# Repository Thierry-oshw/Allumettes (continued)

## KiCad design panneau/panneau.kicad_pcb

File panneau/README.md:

# Panelize multiple different designs in KiCAD
Requires KiKit and is based on code from [KiKit](https://github.com/yaqwsx/KiKit/tree/master)

KiKit only allows creating panels of the same design. Creating a panel from multiple boards has too many degrees of freedom to implement in a nice GUI.
Hence, for creating such a panel, a scripting attempt is necessary.

This script creates a simple panel of two different designs of identical dimensions placed above each other.
With including configuration it adds a rail on top and bottom and includes tabs with mouse bites in between boards and between board and rail.

**You will have to adjust the script to your own needs**
This Gist is only meant to provide you with a working example.

## Usage
Install KiKit, start KiCAD command prompt, navigate to appropriate directory, run `python panelize_multiple.py`

## License
Derived from KiKit. Same MIT license.

## Versions
Tested with KiCAD 7 and KiKit 1.1.0

## faire "python panelize_multiple.py" dans le cli kicad
puis changer les v-cut en user.1 au lieu de user.comments

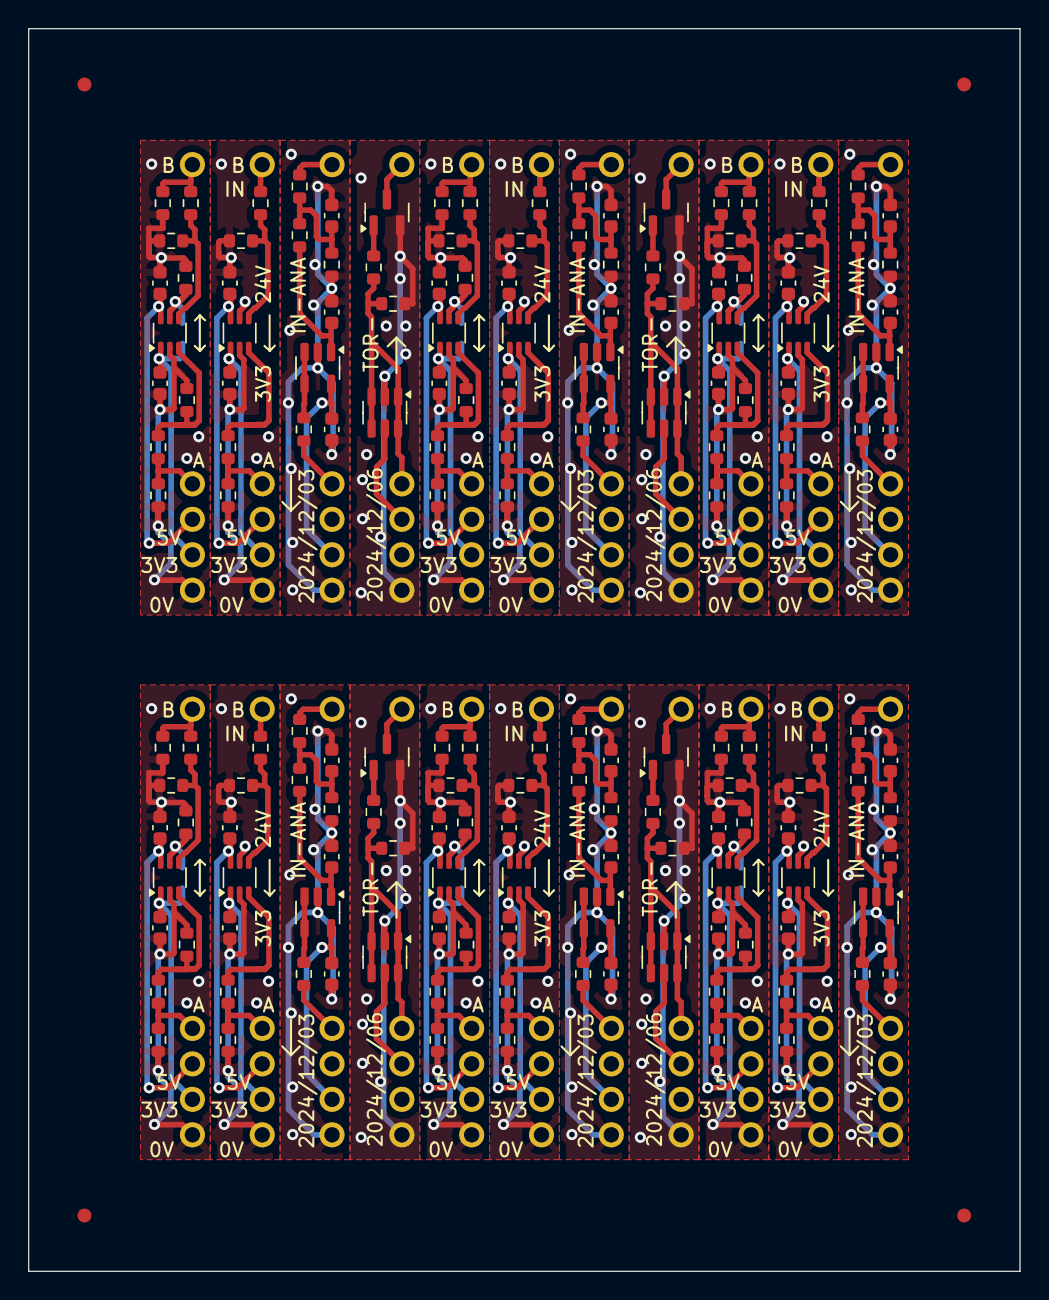
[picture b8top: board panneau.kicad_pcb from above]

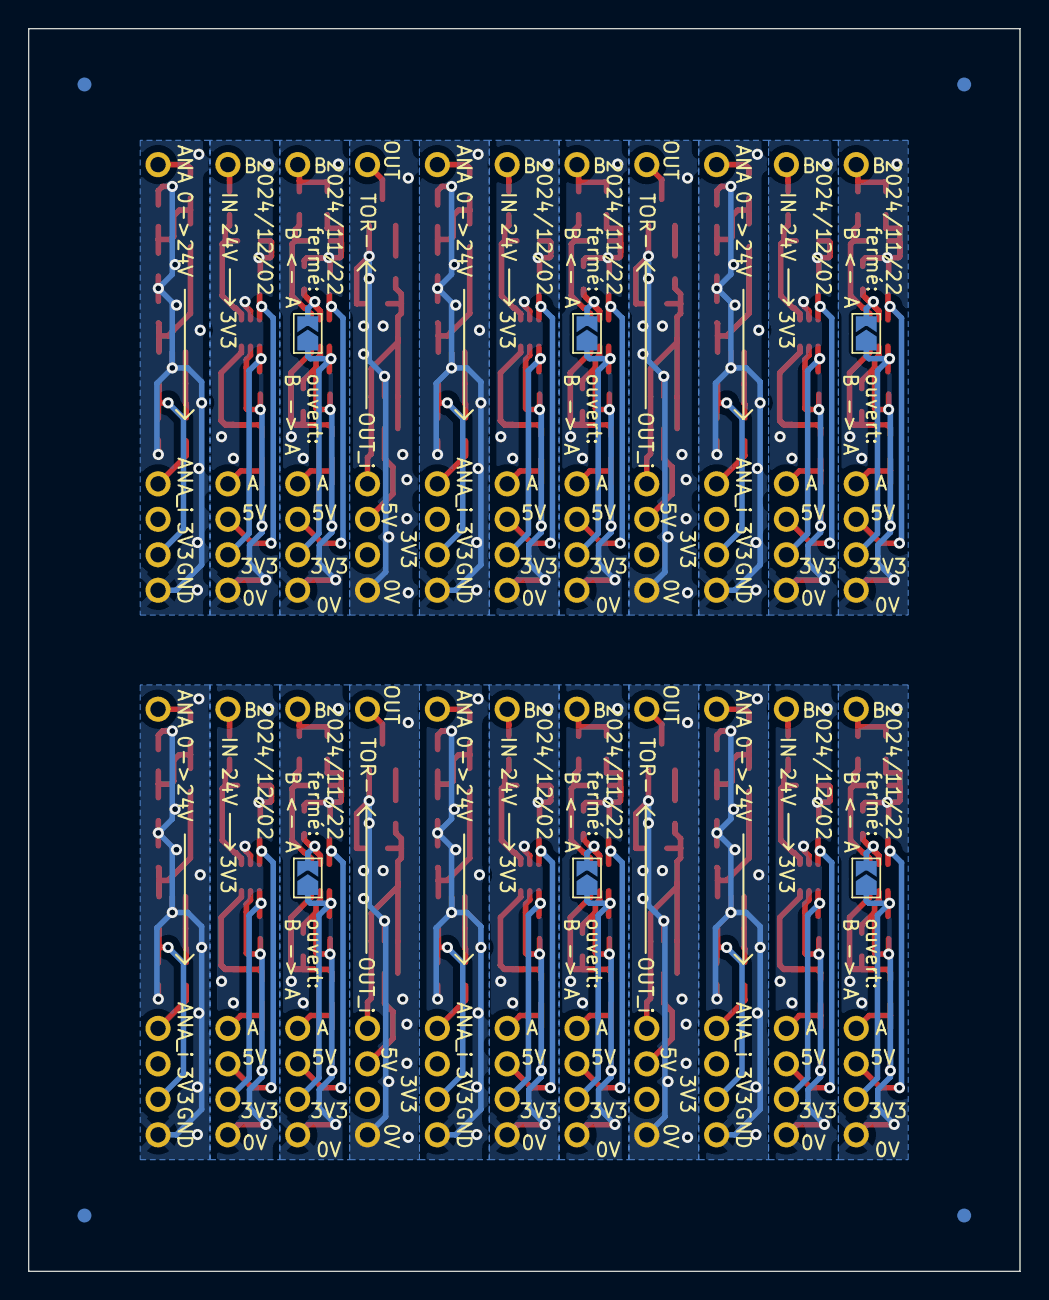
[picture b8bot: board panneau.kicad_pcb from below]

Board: 2 copper layers, 71.0 x 89.0 mm, 290 parts (10 on the bottom side), 152 nets.

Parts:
Board_0-C1, Board_0-C2, Board_1-C1, Board_1-C2, Board_2-C1, Board_2-C9, Board_4-C1, Board_4-C2, Board_5-C1, Board_5-C2, Board_6-C1, Board_6-C9, Board_8-C1, Board_8-C2, Board_9-C1, Board_9-C2, Board_10-C1, Board_10-C9, Board_11-C1, Board_11-C2, Board_12-C1, Board_12-C2, Board_13-C1, Board_13-C9, Board_15-C1, Board_15-C2, Board_16-C1, Board_16-C2, Board_17-C1, Board_17-C9, Board_19-C1, Board_19-C2, Board_20-C1, Board_20-C2, Board_21-C1, Board_21-C9: 100nF 50V X7R; C_0603_1608Metric
Board_0-JP1, Board_4-JP1, Board_8-JP1, Board_11-JP1, Board_15-JP1, Board_19-JP1: SolderJumper_2_Open; SolderJumper-2_P1.3mm_Open_TrianglePad1.0x1.5mm
Board_0-R1, Board_0-R4, Board_0-R7, Board_1-R1, Board_3-R1, Board_4-R1, Board_4-R4, Board_4-R7, Board_5-R1, Board_7-R1, Board_8-R1, Board_8-R4, Board_8-R7, Board_9-R1, Board_11-R1, Board_11-R4, Board_11-R7, Board_12-R1, Board_14-R1, Board_15-R1, Board_15-R4, Board_15-R7, Board_16-R1, Board_18-R1, Board_19-R1, Board_19-R4, Board_19-R7, Board_20-R1: 100k; R_0603_1608Metric
Board_0-R2, Board_0-R6, Board_1-R2, Board_2-R9, Board_2-R13, Board_4-R2, Board_4-R6, Board_5-R2, Board_6-R9, Board_6-R13, Board_8-R2, Board_8-R6, Board_9-R2, Board_10-R9, Board_10-R13, Board_11-R2, Board_11-R6, Board_12-R2, Board_13-R9, Board_13-R13, Board_15-R2, Board_15-R6, Board_16-R2, Board_17-R9, Board_17-R13, Board_19-R2, Board_19-R6, Board_20-R2, Board_21-R9, Board_21-R13: 1k; R_0603_1608Metric
Board_0-R3, Board_0-R5, Board_4-R3, Board_4-R5, Board_8-R3, Board_8-R5, Board_11-R3, Board_11-R5, Board_15-R3, Board_15-R5, Board_19-R3, Board_19-R5: NM; R_0603_1608Metric
Board_0-TP1, Board_0-TP2, Board_0-TP3, Board_0-TP4, Board_0-TP5, Board_1-TP1, Board_1-TP2, Board_1-TP3, Board_1-TP4, Board_1-TP5, Board_2-TP1, Board_2-TP2, Board_2-TP3, Board_2-TP4, Board_2-TP5, Board_3-TP1, Board_3-TP2, Board_3-TP3, Board_3-TP4, Board_3-TP5, Board_4-TP1, Board_4-TP2, Board_4-TP3, Board_4-TP4, Board_4-TP5, Board_5-TP1, Board_5-TP2, Board_5-TP3, Board_5-TP4, Board_5-TP5, Board_6-TP1, Board_6-TP2, Board_6-TP3, Board_6-TP4, Board_6-TP5, Board_7-TP1, Board_7-TP2, Board_7-TP3, Board_7-TP4, Board_7-TP5, Board_8-TP1, Board_8-TP2, Board_8-TP3, Board_8-TP4, Board_8-TP5, Board_9-TP1, Board_9-TP2, Board_9-TP3, Board_9-TP4, Board_9-TP5, Board_10-TP1, Board_10-TP2, Board_10-TP3, Board_10-TP4, Board_10-TP5, Board_11-TP1, Board_11-TP2, Board_11-TP3, Board_11-TP4, Board_11-TP5, Board_12-TP1, Board_12-TP2, Board_12-TP3, Board_12-TP4, Board_12-TP5, Board_13-TP1, Board_13-TP2, Board_13-TP3, Board_13-TP4, Board_13-TP5, Board_14-TP1, Board_14-TP2, Board_14-TP3, Board_14-TP4, Board_14-TP5, Board_15-TP1, Board_15-TP2, Board_15-TP3, Board_15-TP4, Board_15-TP5, Board_16-TP1, Board_16-TP2, Board_16-TP3, Board_16-TP4, Board_16-TP5, Board_17-TP1, Board_17-TP2, Board_17-TP3, Board_17-TP4, Board_17-TP5, Board_18-TP1, Board_18-TP2, Board_18-TP3, Board_18-TP4, Board_18-TP5, Board_19-TP1, Board_19-TP2, Board_19-TP3, Board_19-TP4, Board_19-TP5, Board_20-TP1, Board_20-TP2, Board_20-TP3, Board_20-TP4, Board_20-TP5, Board_21-TP1, Board_21-TP2, Board_21-TP3, Board_21-TP4, Board_21-TP5: TestPoint; Pastille
Board_0-U1, Board_1-U1, Board_4-U1, Board_5-U1, Board_8-U1, Board_9-U1, Board_11-U1, Board_12-U1, Board_15-U1, Board_16-U1, Board_19-U1, Board_20-U1: SN74LVC1T45DCK; SOT-363_SC-70-6
Board_1-R5, Board_5-R5, Board_9-R5, Board_12-R5, Board_16-R5, Board_20-R5: 2k2; R_0603_1608Metric
Board_1-R6, Board_2-R1, Board_5-R6, Board_6-R1, Board_9-R6, Board_10-R1, Board_12-R6, Board_13-R1, Board_16-R6, Board_17-R1, Board_20-R6, Board_21-R1: 10k; R_0603_1608Metric
Board_2-C5, Board_6-C5, Board_10-C5, Board_13-C5, Board_17-C5, Board_21-C5: 1nF 50V X7R; C_0603_1608Metric
Board_2-R2, Board_6-R2, Board_10-R2, Board_13-R2, Board_17-R2, Board_21-R2: 1k5; R_0603_1608Metric
Board_2-U1, Board_6-U1, Board_10-U1, Board_13-U1, Board_17-U1, Board_21-U1: LMV321; SOT-23-5
Board_3-Q1, Board_7-Q1, Board_14-Q1, Board_18-Q1: AO3400A; SOT-23
Board_3-R2, Board_7-R2, Board_14-R2, Board_18-R2: 0R; R_0603_1608Metric
Board_3-U1, Board_7-U1, Board_14-U1, Board_18-U1: SRV05-4; SOT-23-6
KiKit_FID_B_1, KiKit_FID_B_2, KiKit_FID_B_3, KiKit_FID_B_4: Fiducial
KiKit_FID_T_1, KiKit_FID_T_2, KiKit_FID_T_3, KiKit_FID_T_4: Fiducial

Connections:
Board_0-/3V3: Board_0-C1.1, Board_0-JP1.1 (A), Board_0-TP4.1, Board_0-U1.1 (VCCA)
Board_0-/5V: Board_0-C2.1, Board_0-TP3.1, Board_0-U1.6 (VCCB)
Board_0-/GND: Board_0-C1.2, Board_0-C2.2, Board_0-R1.2, Board_0-R3.2, Board_0-R4.2, Board_0-R5.2, Board_0-R7.2, Board_0-TP5.1, Board_0-U1.2 (GND)
Board_0-/OUT: Board_0-R6.2, Board_0-R7.1, Board_0-TP1.1
Board_0-/OUT_i: Board_0-R1.1, Board_0-R2.1, Board_0-TP2.1
Board_0-Net-(JP1-B): Board_0-JP1.2 (B), Board_0-R4.1, Board_0-U1.5 (DIR)
Board_0-Net-(U1-A): Board_0-R2.2, Board_0-R3.1, Board_0-U1.3 (A)
Board_0-Net-(U1-B): Board_0-R5.1, Board_0-R6.1, Board_0-U1.4 (B)
Board_1-/3V3: Board_1-C1.1, Board_1-TP4.1, Board_1-U1.1 (VCCA)
Board_1-/5V: Board_1-C2.1, Board_1-TP3.1, Board_1-U1.6 (VCCB)
Board_1-/GND: Board_1-C1.2, Board_1-C2.2, Board_1-R1.2, Board_1-R5.2, Board_1-TP5.1, Board_1-U1.2 (GND), Board_1-U1.5 (DIR)
Board_1-/IN: Board_1-R6.2, Board_1-TP1.1
Board_1-/IN_i: Board_1-R1.1, Board_1-R2.1, Board_1-TP2.1
Board_1-Net-(U1-A): Board_1-R2.2, Board_1-U1.3 (A)
Board_1-Net-(U1-B): Board_1-R5.1, Board_1-R6.1, Board_1-U1.4 (B)
Board_2-/3V3: Board_2-C9.1, Board_2-TP3.1, Board_2-U1.5 (V+)
Board_2-/ANA: Board_2-R1.2, Board_2-TP1.1
Board_2-/ANA_i: Board_2-R13.2, Board_2-TP2.1
Board_2-/GND: Board_2-C1.2, Board_2-C5.2, Board_2-C9.2, Board_2-R2.1, Board_2-TP4.1, Board_2-U1.2 (V-)
Board_2-Net-(C1-Pad1): Board_2-C1.1, Board_2-R1.1, Board_2-R2.2, Board_2-R9.1
Board_2-Net-(U1-+): Board_2-C5.1, Board_2-R9.2, Board_2-U1.1 (+)
Board_2-Net-(U1--): Board_2-R13.1, Board_2-U1.3 (-), Board_2-U1.4
Board_3-/0V: Board_3-Q1.2 (S), Board_3-R1.2, Board_3-TP5.1, Board_3-U1.2 (VN)
Board_3-/5V: Board_3-TP3.1, Board_3-U1.5 (VP)
Board_3-/OUT: Board_3-Q1.3 (D), Board_3-TP1.1
Board_3-/OUT_i: Board_3-R1.1, Board_3-R2.1, Board_3-TP2.1, Board_3-U1.1 (IO1), Board_3-U1.3 (IO2), Board_3-U1.4 (IO3), Board_3-U1.6 (IO4)
Board_3-Net-(Q1-G): Board_3-Q1.1 (G), Board_3-R2.2
Board_4-/3V3: Board_4-C1.1, Board_4-JP1.1 (A), Board_4-TP4.1, Board_4-U1.1 (VCCA)
Board_4-/5V: Board_4-C2.1, Board_4-TP3.1, Board_4-U1.6 (VCCB)
Board_4-/GND: Board_4-C1.2, Board_4-C2.2, Board_4-R1.2, Board_4-R3.2, Board_4-R4.2, Board_4-R5.2, Board_4-R7.2, Board_4-TP5.1, Board_4-U1.2 (GND)
Board_4-/OUT: Board_4-R6.2, Board_4-R7.1, Board_4-TP1.1
Board_4-/OUT_i: Board_4-R1.1, Board_4-R2.1, Board_4-TP2.1
Board_4-Net-(JP1-B): Board_4-JP1.2 (B), Board_4-R4.1, Board_4-U1.5 (DIR)
Board_4-Net-(U1-A): Board_4-R2.2, Board_4-R3.1, Board_4-U1.3 (A)
Board_4-Net-(U1-B): Board_4-R5.1, Board_4-R6.1, Board_4-U1.4 (B)
Board_5-/3V3: Board_5-C1.1, Board_5-TP4.1, Board_5-U1.1 (VCCA)
Board_5-/5V: Board_5-C2.1, Board_5-TP3.1, Board_5-U1.6 (VCCB)
Board_5-/GND: Board_5-C1.2, Board_5-C2.2, Board_5-R1.2, Board_5-R5.2, Board_5-TP5.1, Board_5-U1.2 (GND), Board_5-U1.5 (DIR)
Board_5-/IN: Board_5-R6.2, Board_5-TP1.1
Board_5-/IN_i: Board_5-R1.1, Board_5-R2.1, Board_5-TP2.1
Board_5-Net-(U1-A): Board_5-R2.2, Board_5-U1.3 (A)
Board_5-Net-(U1-B): Board_5-R5.1, Board_5-R6.1, Board_5-U1.4 (B)
Board_6-/3V3: Board_6-C9.1, Board_6-TP3.1, Board_6-U1.5 (V+)
Board_6-/ANA: Board_6-R1.2, Board_6-TP1.1
Board_6-/ANA_i: Board_6-R13.2, Board_6-TP2.1
Board_6-/GND: Board_6-C1.2, Board_6-C5.2, Board_6-C9.2, Board_6-R2.1, Board_6-TP4.1, Board_6-U1.2 (V-)
Board_6-Net-(C1-Pad1): Board_6-C1.1, Board_6-R1.1, Board_6-R2.2, Board_6-R9.1
Board_6-Net-(U1-+): Board_6-C5.1, Board_6-R9.2, Board_6-U1.1 (+)
Board_6-Net-(U1--): Board_6-R13.1, Board_6-U1.3 (-), Board_6-U1.4
Board_7-/0V: Board_7-Q1.2 (S), Board_7-R1.2, Board_7-TP5.1, Board_7-U1.2 (VN)
Board_7-/5V: Board_7-TP3.1, Board_7-U1.5 (VP)
Board_7-/OUT: Board_7-Q1.3 (D), Board_7-TP1.1
Board_7-/OUT_i: Board_7-R1.1, Board_7-R2.1, Board_7-TP2.1, Board_7-U1.1 (IO1), Board_7-U1.3 (IO2), Board_7-U1.4 (IO3), Board_7-U1.6 (IO4)
Board_7-Net-(Q1-G): Board_7-Q1.1 (G), Board_7-R2.2
Board_8-/3V3: Board_8-C1.1, Board_8-JP1.1 (A), Board_8-TP4.1, Board_8-U1.1 (VCCA)
Board_8-/5V: Board_8-C2.1, Board_8-TP3.1, Board_8-U1.6 (VCCB)
Board_8-/GND: Board_8-C1.2, Board_8-C2.2, Board_8-R1.2, Board_8-R3.2, Board_8-R4.2, Board_8-R5.2, Board_8-R7.2, Board_8-TP5.1, Board_8-U1.2 (GND)
Board_8-/OUT: Board_8-R6.2, Board_8-R7.1, Board_8-TP1.1
Board_8-/OUT_i: Board_8-R1.1, Board_8-R2.1, Board_8-TP2.1
Board_8-Net-(JP1-B): Board_8-JP1.2 (B), Board_8-R4.1, Board_8-U1.5 (DIR)
Board_8-Net-(U1-A): Board_8-R2.2, Board_8-R3.1, Board_8-U1.3 (A)
Board_8-Net-(U1-B): Board_8-R5.1, Board_8-R6.1, Board_8-U1.4 (B)
Board_9-/3V3: Board_9-C1.1, Board_9-TP4.1, Board_9-U1.1 (VCCA)
Board_9-/5V: Board_9-C2.1, Board_9-TP3.1, Board_9-U1.6 (VCCB)
Board_9-/GND: Board_9-C1.2, Board_9-C2.2, Board_9-R1.2, Board_9-R5.2, Board_9-TP5.1, Board_9-U1.2 (GND), Board_9-U1.5 (DIR)
Board_9-/IN: Board_9-R6.2, Board_9-TP1.1
Board_9-/IN_i: Board_9-R1.1, Board_9-R2.1, Board_9-TP2.1
Board_9-Net-(U1-A): Board_9-R2.2, Board_9-U1.3 (A)
Board_9-Net-(U1-B): Board_9-R5.1, Board_9-R6.1, Board_9-U1.4 (B)
Board_10-/3V3: Board_10-C9.1, Board_10-TP3.1, Board_10-U1.5 (V+)
Board_10-/ANA: Board_10-R1.2, Board_10-TP1.1
Board_10-/ANA_i: Board_10-R13.2, Board_10-TP2.1
Board_10-/GND: Board_10-C1.2, Board_10-C5.2, Board_10-C9.2, Board_10-R2.1, Board_10-TP4.1, Board_10-U1.2 (V-)
Board_10-Net-(C1-Pad1): Board_10-C1.1, Board_10-R1.1, Board_10-R2.2, Board_10-R9.1
Board_10-Net-(U1-+): Board_10-C5.1, Board_10-R9.2, Board_10-U1.1 (+)
Board_10-Net-(U1--): Board_10-R13.1, Board_10-U1.3 (-), Board_10-U1.4
Board_11-/3V3: Board_11-C1.1, Board_11-JP1.1 (A), Board_11-TP4.1, Board_11-U1.1 (VCCA)
Board_11-/5V: Board_11-C2.1, Board_11-TP3.1, Board_11-U1.6 (VCCB)
Board_11-/GND: Board_11-C1.2, Board_11-C2.2, Board_11-R1.2, Board_11-R3.2, Board_11-R4.2, Board_11-R5.2, Board_11-R7.2, Board_11-TP5.1, Board_11-U1.2 (GND)
Board_11-/OUT: Board_11-R6.2, Board_11-R7.1, Board_11-TP1.1
Board_11-/OUT_i: Board_11-R1.1, Board_11-R2.1, Board_11-TP2.1
Board_11-Net-(JP1-B): Board_11-JP1.2 (B), Board_11-R4.1, Board_11-U1.5 (DIR)
Board_11-Net-(U1-A): Board_11-R2.2, Board_11-R3.1, Board_11-U1.3 (A)
Board_11-Net-(U1-B): Board_11-R5.1, Board_11-R6.1, Board_11-U1.4 (B)
Board_12-/3V3: Board_12-C1.1, Board_12-TP4.1, Board_12-U1.1 (VCCA)
Board_12-/5V: Board_12-C2.1, Board_12-TP3.1, Board_12-U1.6 (VCCB)
Board_12-/GND: Board_12-C1.2, Board_12-C2.2, Board_12-R1.2, Board_12-R5.2, Board_12-TP5.1, Board_12-U1.2 (GND), Board_12-U1.5 (DIR)
Board_12-/IN: Board_12-R6.2, Board_12-TP1.1
Board_12-/IN_i: Board_12-R1.1, Board_12-R2.1, Board_12-TP2.1
Board_12-Net-(U1-A): Board_12-R2.2, Board_12-U1.3 (A)
Board_12-Net-(U1-B): Board_12-R5.1, Board_12-R6.1, Board_12-U1.4 (B)
Board_13-/3V3: Board_13-C9.1, Board_13-TP3.1, Board_13-U1.5 (V+)
Board_13-/ANA: Board_13-R1.2, Board_13-TP1.1
Board_13-/ANA_i: Board_13-R13.2, Board_13-TP2.1
Board_13-/GND: Board_13-C1.2, Board_13-C5.2, Board_13-C9.2, Board_13-R2.1, Board_13-TP4.1, Board_13-U1.2 (V-)
Board_13-Net-(C1-Pad1): Board_13-C1.1, Board_13-R1.1, Board_13-R2.2, Board_13-R9.1
Board_13-Net-(U1-+): Board_13-C5.1, Board_13-R9.2, Board_13-U1.1 (+)
Board_13-Net-(U1--): Board_13-R13.1, Board_13-U1.3 (-), Board_13-U1.4
Board_14-/0V: Board_14-Q1.2 (S), Board_14-R1.2, Board_14-TP5.1, Board_14-U1.2 (VN)
Board_14-/5V: Board_14-TP3.1, Board_14-U1.5 (VP)
Board_14-/OUT: Board_14-Q1.3 (D), Board_14-TP1.1
Board_14-/OUT_i: Board_14-R1.1, Board_14-R2.1, Board_14-TP2.1, Board_14-U1.1 (IO1), Board_14-U1.3 (IO2), Board_14-U1.4 (IO3), Board_14-U1.6 (IO4)
Board_14-Net-(Q1-G): Board_14-Q1.1 (G), Board_14-R2.2
Board_15-/3V3: Board_15-C1.1, Board_15-JP1.1 (A), Board_15-TP4.1, Board_15-U1.1 (VCCA)
Board_15-/5V: Board_15-C2.1, Board_15-TP3.1, Board_15-U1.6 (VCCB)
Board_15-/GND: Board_15-C1.2, Board_15-C2.2, Board_15-R1.2, Board_15-R3.2, Board_15-R4.2, Board_15-R5.2, Board_15-R7.2, Board_15-TP5.1, Board_15-U1.2 (GND)
Board_15-/OUT: Board_15-R6.2, Board_15-R7.1, Board_15-TP1.1
Board_15-/OUT_i: Board_15-R1.1, Board_15-R2.1, Board_15-TP2.1
Board_15-Net-(JP1-B): Board_15-JP1.2 (B), Board_15-R4.1, Board_15-U1.5 (DIR)
Board_15-Net-(U1-A): Board_15-R2.2, Board_15-R3.1, Board_15-U1.3 (A)
Board_15-Net-(U1-B): Board_15-R5.1, Board_15-R6.1, Board_15-U1.4 (B)
Board_16-/3V3: Board_16-C1.1, Board_16-TP4.1, Board_16-U1.1 (VCCA)
Board_16-/5V: Board_16-C2.1, Board_16-TP3.1, Board_16-U1.6 (VCCB)
Board_16-/GND: Board_16-C1.2, Board_16-C2.2, Board_16-R1.2, Board_16-R5.2, Board_16-TP5.1, Board_16-U1.2 (GND), Board_16-U1.5 (DIR)
Board_16-/IN: Board_16-R6.2, Board_16-TP1.1
Board_16-/IN_i: Board_16-R1.1, Board_16-R2.1, Board_16-TP2.1
Board_16-Net-(U1-A): Board_16-R2.2, Board_16-U1.3 (A)
Board_16-Net-(U1-B): Board_16-R5.1, Board_16-R6.1, Board_16-U1.4 (B)
Board_17-/3V3: Board_17-C9.1, Board_17-TP3.1, Board_17-U1.5 (V+)
Board_17-/ANA: Board_17-R1.2, Board_17-TP1.1
Board_17-/ANA_i: Board_17-R13.2, Board_17-TP2.1
Board_17-/GND: Board_17-C1.2, Board_17-C5.2, Board_17-C9.2, Board_17-R2.1, Board_17-TP4.1, Board_17-U1.2 (V-)
Board_17-Net-(C1-Pad1): Board_17-C1.1, Board_17-R1.1, Board_17-R2.2, Board_17-R9.1
Board_17-Net-(U1-+): Board_17-C5.1, Board_17-R9.2, Board_17-U1.1 (+)
Board_17-Net-(U1--): Board_17-R13.1, Board_17-U1.3 (-), Board_17-U1.4
Board_18-/0V: Board_18-Q1.2 (S), Board_18-R1.2, Board_18-TP5.1, Board_18-U1.2 (VN)
Board_18-/5V: Board_18-TP3.1, Board_18-U1.5 (VP)
Board_18-/OUT: Board_18-Q1.3 (D), Board_18-TP1.1
Board_18-/OUT_i: Board_18-R1.1, Board_18-R2.1, Board_18-TP2.1, Board_18-U1.1 (IO1), Board_18-U1.3 (IO2), Board_18-U1.4 (IO3), Board_18-U1.6 (IO4)
Board_18-Net-(Q1-G): Board_18-Q1.1 (G), Board_18-R2.2
Board_19-/3V3: Board_19-C1.1, Board_19-JP1.1 (A), Board_19-TP4.1, Board_19-U1.1 (VCCA)
Board_19-/5V: Board_19-C2.1, Board_19-TP3.1, Board_19-U1.6 (VCCB)
Board_19-/GND: Board_19-C1.2, Board_19-C2.2, Board_19-R1.2, Board_19-R3.2, Board_19-R4.2, Board_19-R5.2, Board_19-R7.2, Board_19-TP5.1, Board_19-U1.2 (GND)
Board_19-/OUT: Board_19-R6.2, Board_19-R7.1, Board_19-TP1.1
Board_19-/OUT_i: Board_19-R1.1, Board_19-R2.1, Board_19-TP2.1
Board_19-Net-(JP1-B): Board_19-JP1.2 (B), Board_19-R4.1, Board_19-U1.5 (DIR)
Board_19-Net-(U1-A): Board_19-R2.2, Board_19-R3.1, Board_19-U1.3 (A)
Board_19-Net-(U1-B): Board_19-R5.1, Board_19-R6.1, Board_19-U1.4 (B)
Board_20-/3V3: Board_20-C1.1, Board_20-TP4.1, Board_20-U1.1 (VCCA)
Board_20-/5V: Board_20-C2.1, Board_20-TP3.1, Board_20-U1.6 (VCCB)
Board_20-/GND: Board_20-C1.2, Board_20-C2.2, Board_20-R1.2, Board_20-R5.2, Board_20-TP5.1, Board_20-U1.2 (GND), Board_20-U1.5 (DIR)
Board_20-/IN: Board_20-R6.2, Board_20-TP1.1
Board_20-/IN_i: Board_20-R1.1, Board_20-R2.1, Board_20-TP2.1
Board_20-Net-(U1-A): Board_20-R2.2, Board_20-U1.3 (A)
Board_20-Net-(U1-B): Board_20-R5.1, Board_20-R6.1, Board_20-U1.4 (B)
Board_21-/3V3: Board_21-C9.1, Board_21-TP3.1, Board_21-U1.5 (V+)
Board_21-/ANA: Board_21-R1.2, Board_21-TP1.1
Board_21-/ANA_i: Board_21-R13.2, Board_21-TP2.1
Board_21-/GND: Board_21-C1.2, Board_21-C5.2, Board_21-C9.2, Board_21-R2.1, Board_21-TP4.1, Board_21-U1.2 (V-)
Board_21-Net-(C1-Pad1): Board_21-C1.1, Board_21-R1.1, Board_21-R2.2, Board_21-R9.1
Board_21-Net-(U1-+): Board_21-C5.1, Board_21-R9.2, Board_21-U1.1 (+)
Board_21-Net-(U1--): Board_21-R13.1, Board_21-U1.3 (-), Board_21-U1.4

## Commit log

2024-11-22 prête
2024-11-29 gerbers centrés
2024-12-02 IN-24V : creation
2024-12-03 correction cartouche
2024-12-03 IN-24V
    correction cartouche
2024-12-03 IN_ANA creation
2024-12-06 OUT_TORM : creation
2025-02-21 BIDIR : passage à kicad 9
2025-02-21 IN_24V : kicad 9
2025-02-21 IN_ANA : kicad 9
2025-02-21 OUT_TORM: kicad 9
2025-02-27 BIDIR_5V : chemin librairies corrigées suite à maj
2025-02-28 BIDIR_5V : correction plan de masse
2025-02-28 IN_24V : correction des plans de masse
2025-02-28 IN_ANA: correction des plans de masse
2025-02-28 OUT_TORM : correction des plans de masse
    et de l'épaisseur définie
2025-02-28 IN_ANA : correction épaisseur
2025-02-28 panneau : stable
2025-03-13 allumettes : maj V-cut
2025-04-21 XCAN : premier jet
2025-05-01 DCDC_5V : création
2025-10-29 maj gitignore
2025-10-29 retouche pour 10mm de large
2025-10-30 sauvegarde des fichiers bom et positions
2025-10-30 fabrication
2025-11-10 Ajout champ lié à maj kicad
2025-11-10 OSC_1 : premier jet
2025-12-24 IN-24V passage à opto et nouveau format
